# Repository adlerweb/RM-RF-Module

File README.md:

# RM-RF-Module

This system can be used to add RF functionality to ordinary photoelectric smoke detectors based on the widespread MC145010 IC or its derivatives.

The module uses RF24 2.4GHz transceivers and communicates with a central receiver. In addition to relaying the smoke alarm it also features a DS18B20 temperature sensor and will report high temperature conditions. Lastly I'll - even if no alarm is active - report battery voltage and temperature back to the central receiver in regular intervals to allow for statistics and detect broken detectors.

Power can be supplied using the original 9V battery or a protected 7.4V lithium battery pack.

Real time communication or mesh functionality is not implemented to keep power consumption down. It should be possible to use nodes as relays using this concept, but nothing has been implemented so far.

Please consider this project as WIP - if you're looking for a system that "just works" you're probably better off with a commercial system.
More details in German can be found in the design and build vlog over at HTTPS://www.youtube.com/user/adlerweb/search?query=rauchmelder

# Warning

Modifying detectors will void their approval. If you're required to install smoke detectors modified modules are not sufficient to pass the requirements. Use at your own risk.

# Repo

## Hardware

The module is based on a cheap ATTiny88 as central processor and an NRF24L01+ for radio communication. The 3.3V system power uses a NCP551 featuring a rather low quiescent current for it's price to keep consumption down. Peripherals like the radio module or an optional DS18B20 are only powered up when accessed.

The original smoke alarm uses the IO-functionality of the MC145010 detector IC. Additionally the onboard LED and (optionally) the switch are interfaced. Since the board is based on an older design with full separation the interface uses optocouplers between detector and this PCB. There is however no galvanic isolation. It should be possible to switch to a transistor based approach and shrink the PCB if desired.

## Software

### Basic function

All system timing is based on the regular LED flash of the original smoke detector IC. In my case it blinks every 20 seconds.

When booting for the first time all used GPIOs will be prepared and a boot message transmitted to the master.

Now the IO pin is checked for an alarm condition, if there is one an alarm message with type 1 will be transmitted.
Next - if the configured number of LED flashes for temperature is reached - the temperature sensor will be powered up and checked. If the measured temperature is above a defined alarm level an alarm message with type 2 will be transmitted
Now - if the configured number of LED flashes for the alive-message is reached - it will power up the temperature sensor and ADC, measure both and send the results to the master
Lastly it ensures the detectors LED is turned off, rearms the LED-flash-interrupt and enters power-down-mode.

### RF-Notes

NRF24L01+ only supports listening to 6 FIFOs at a time. While it is possible to target a single FIFO from multiple senders there are reports this would mess up the auto-ACK-feature in some cases and as such provide only unreliable communication. The code uses an additional checksum and acknowledgement layer to ensure proper transmission. Inside the ACK the master can piggyback a 2-byte-value to send commands to the smoke detector.

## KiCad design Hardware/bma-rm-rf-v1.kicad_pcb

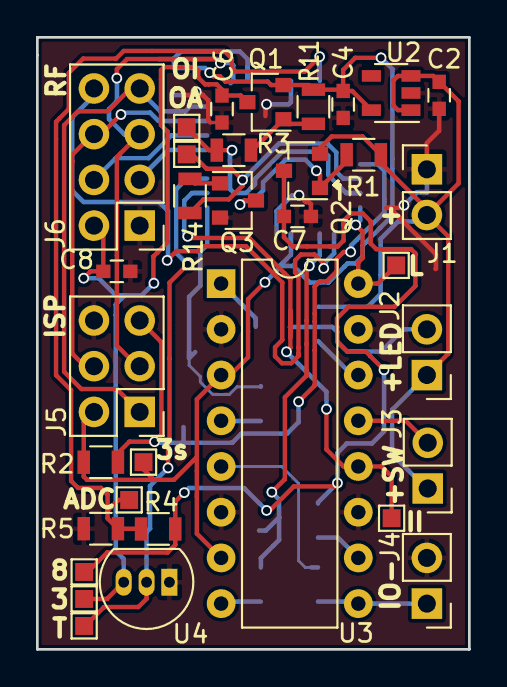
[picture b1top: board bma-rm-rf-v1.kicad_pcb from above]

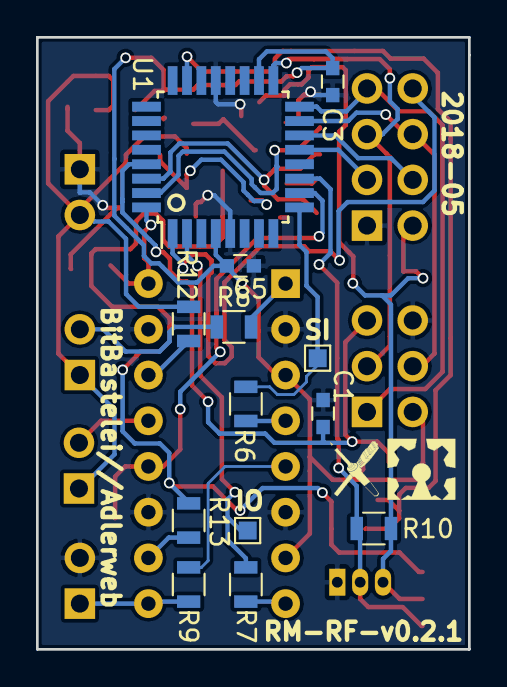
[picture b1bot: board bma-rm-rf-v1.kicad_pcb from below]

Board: 2 copper layers, 24.0 x 34.0 mm, 46 parts (13 on the bottom side), 32 nets.

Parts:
C1, C2, C3, C4, C5, C6, C7, C8: 100n; C_0603
J1: PWR; Pin_Header_Straight_1x02_Pitch2.54mm
J2: RM_LED; Pin_Header_Straight_1x02_Pitch2.54mm
J3: RM_SW; Pin_Header_Straight_1x02_Pitch2.54mm
J4: RM_IO; Pin_Header_Straight_1x02_Pitch2.54mm
J5: ISP; Pin_Header_Straight_2x03_Pitch2.54mm
J6: NRF24L01; Pin_Header_Straight_2x04_Pitch2.54mm
Q1, Q2: AO3407; SOT-23
Q3: SI2302DS; SOT-23
R1, R11: 560k; R_0805
R2, R10: 10k; R_0805
R3, R8, R9, R12, R13, R14: 1.8k; R_0805
R4: 22k; R_0805
R5: 12k; R_0805
R6, R7: 470; R_0805
TP1, TP2, TP3, TP4, TP5, TP6, TP7, TP8, TP9, TP10, TP11: TEST; Test_Point_Pad_1.0x1.0mm
U1: ATTINY88-AU; TQFP-32_7x7mm_Pitch0.8mm
U2: NCP551; SOT-23-5
U3: PC847; DIP-16_W7.62mm
U4: DS18B20; TO-92_Inline_Narrow_Oval

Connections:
+3.3VP: C6.1, C8.2, J6.2, Q1.3, R10.2, TP2.1, U4.3
+3V3: C3.1, C4.1, C5.1, J5.2, Q1.2, R2.1, R11.2, TP5.1, U1.4, U1.18, U2.5, U3.3, U3.7
+BATT: C2.1, J1.2, J2.1, J3.1, Q2.2, R1.2, R12.1, U2.1, U2.3
CE: J6.3, U1.13
CSN: J6.4, U1.14
GND: C1.1, C2.2, C3.2, C4.2, C5.2, C6.2, C7.2, C8.1, J1.1, J4.2, J5.6, J6.1, Q3.2, R5.2, U1.5, U1.21, U2.2, U3.2, U3.6, U3.11, U3.15, U4.1
INT0: J6.8, U1.1
MISO: J5.1, J6.7, U1.16
MOSI: J5.4, J6.6, U1.15
unnamed: J2.2, R8.1
unnamed: J3.2, U3.13
unnamed: J4.1, R9.1, U3.9
unnamed: Q1.1, R3.2, R11.1
unnamed: Q2.1, Q3.3, R1.1
unnamed: Q3.1, R14.2
unnamed: R4.2, R5.1, TP6.1, U1.23
unnamed: R6.1, U3.4
unnamed: R7.1, U3.8
unnamed: R8.2, U3.1
unnamed: R9.2, U3.5
unnamed: R12.2, U3.14
unnamed: R13.2, U3.10
PWR_ON_ADC: R14.1, TP3.1, U1.30
PWR_ON_IO: R3.1, TP1.1, U1.31
RESET: C1.2, J5.5, R2.2, U1.29
R_IO_I: TP10.1, U1.10, U3.12
R_IO_O: R7.2, TP9.1, U1.2
R_LED: TP8.1, U1.32, U3.16
R_SW: R6.2, TP7.1, U1.9
SCK: J5.3, J6.5, U1.17
TEMP: R10.1, TP11.1, U1.11, U4.2
VPP: C7.1, Q2.3, R4.1, R13.1, TP4.1

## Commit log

2018-05-19 Import
2018-05-19 Readme: Remove GUI-fsckup
    How can this diff control line even be saved into the file, GIT? How? >_>
